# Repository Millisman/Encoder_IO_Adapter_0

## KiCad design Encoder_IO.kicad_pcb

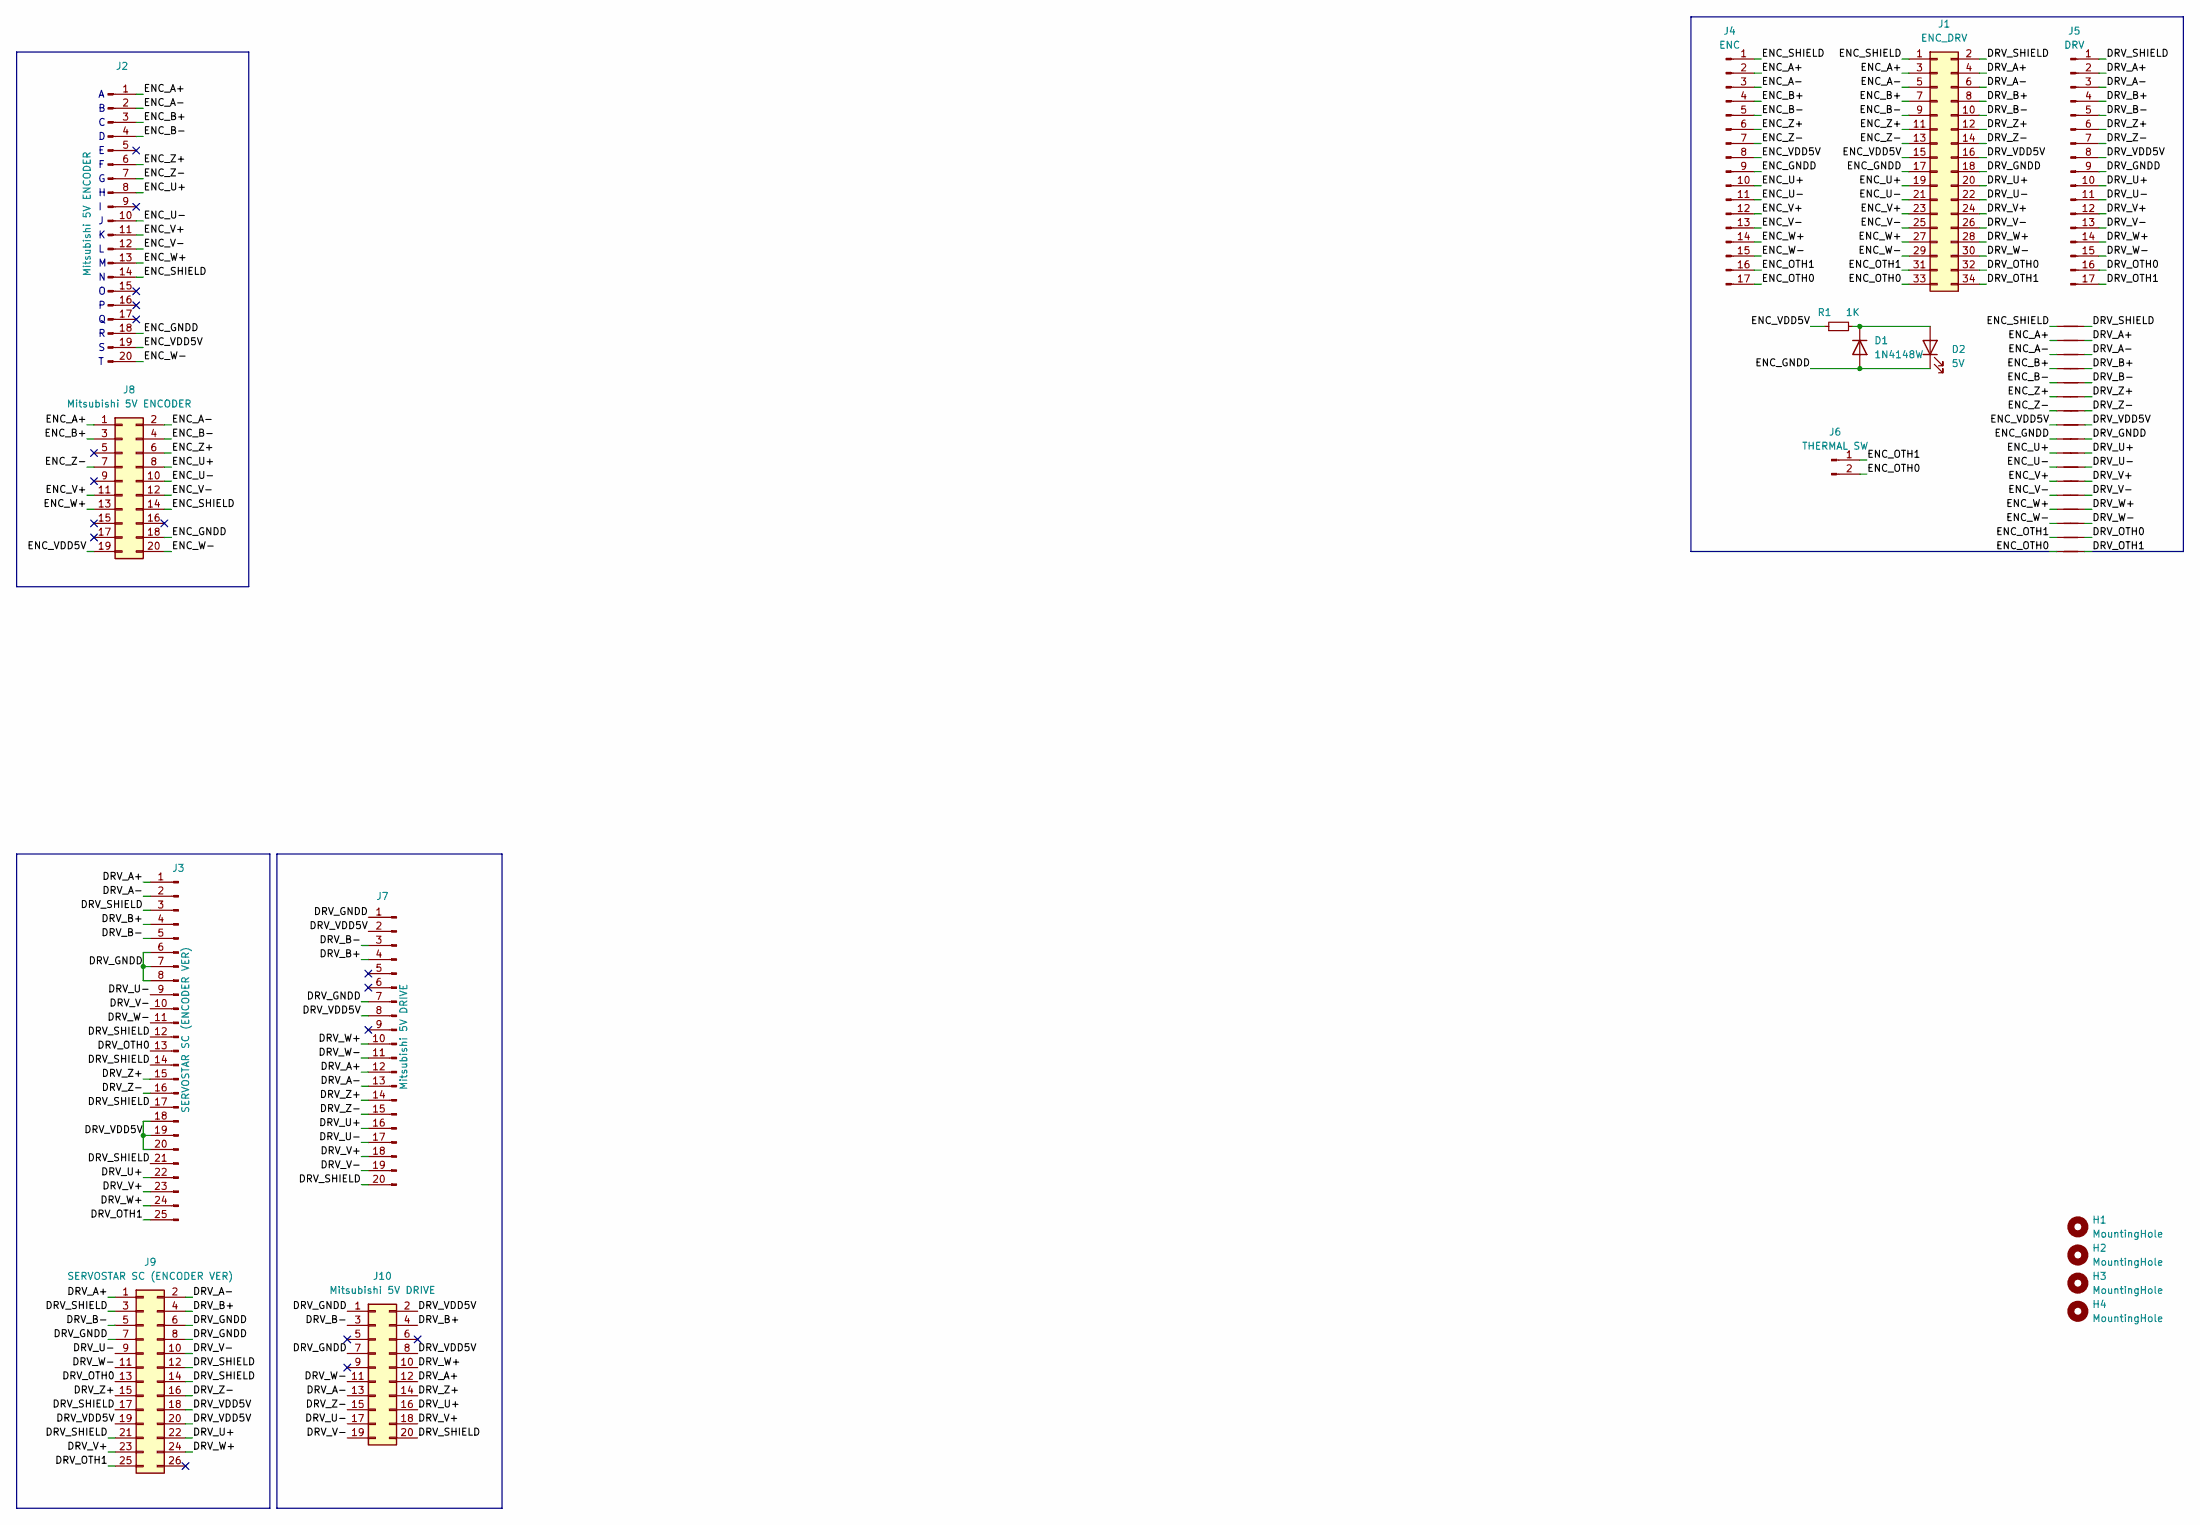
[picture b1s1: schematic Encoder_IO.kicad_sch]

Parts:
D1: 1N4148W; D_SOD-323_HandSoldering
D2: 5V; LED_0805_2012Metric_Pad1.15x1.40mm_HandSolder
H1, H2, H3, H4: MountingHole; MountingHole_3.2mm_M3
J1: ENC_DRV; PinHeader_2x17_P2.54mm_Vertical
J2: Mitsubishi 5V ENCODER; PinHeader_1x20_P2.54mm_Vertical
J3: SERVOSTAR SC (ENCODER VER); PinHeader_1x25_P2.54mm_Vertical
J4: ENC; PinHeader_1x17_P2.54mm_Vertical
J5: DRV; PinHeader_1x17_P2.54mm_Vertical
J6: THERMAL SW; PinHeader_1x02_P2.54mm_Vertical
J7: Mitsubishi 5V DRIVE; PinHeader_1x20_P2.54mm_Vertical
J8: Mitsubishi 5V ENCODER; IDC-Header_2x10_P2.54mm_Vertical
J9: SERVOSTAR SC (ENCODER VER); IDC-Header_2x13_P2.54mm_Vertical
J10: Mitsubishi 5V DRIVE; IDC-Header_2x10_P2.54mm_Vertical
NT1, NT2, NT3, NT4, NT5, NT6, NT7, NT8, NT9, NT10, NT11, NT12, NT13, NT14, NT15, NT16, NT17: NetTie_2; NetTie-2_SMD_Pad0.5mm
R1: 1K; R_0805_2012Metric_Pad1.20x1.40mm_HandSolder

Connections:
/DRV_A+: J1.4, J3.1, J5.2, J7.12, J9.1, J10.12, NT2.2
/DRV_A-: J1.6, J3.2, J5.3, J7.13, J9.2, J10.13, NT3.2
/DRV_B+: J1.8, J3.4, J5.4, J7.4, J9.4, J10.4, NT4.2
/DRV_B-: J1.10, J3.5, J5.5, J7.3, J9.5, J10.3, NT5.2
/DRV_GNDD: J1.18, J3.6, J3.7, J3.8, J5.9, J7.1, J7.7, J9.6, J9.7, J9.8, J10.1, J10.7, NT9.2
/DRV_OTH0: J1.32, J3.13, J5.16, J9.13, NT16.2
/DRV_OTH1: J1.34, J3.25, J5.17, J9.25, NT17.2
/DRV_SHIELD: J1.2, J3.3, J3.12, J3.14, J3.17, J3.21, J5.1, J7.20, J9.3, J9.12, J9.14, J9.17, J9.21, J10.20, NT1.2
/DRV_U+: J1.20, J3.22, J5.10, J7.16, J9.22, J10.16, NT10.2
/DRV_U-: J1.22, J3.9, J5.11, J7.17, J9.9, J10.17, NT11.2
/DRV_V+: J1.24, J3.23, J5.12, J7.18, J9.23, J10.18, NT12.2
/DRV_V-: J1.26, J3.10, J5.13, J7.19, J9.10, J10.19, NT13.2
/DRV_VDD5V: J1.16, J3.18, J3.19, J3.20, J5.8, J7.2, J7.8, J9.18, J9.19, J9.20, J10.2, J10.8, NT8.2
/DRV_W+: J1.28, J3.24, J5.14, J7.10, J9.24, J10.10, NT14.2
/DRV_W-: J1.30, J3.11, J5.15, J7.11, J9.11, J10.11, NT15.2
/DRV_Z+: J1.12, J3.15, J5.6, J7.14, J9.15, J10.14, NT6.2
/DRV_Z-: J1.14, J3.16, J5.7, J7.15, J9.16, J10.15, NT7.2
/ENC_A+: J1.3, J2.1, J4.2, J8.1, NT2.1
/ENC_A-: J1.5, J2.2, J4.3, J8.2, NT3.1
/ENC_B+: J1.7, J2.3, J4.4, J8.3, NT4.1
/ENC_B-: J1.9, J2.4, J4.5, J8.4, NT5.1
/ENC_GNDD: D1.2 (A), D2.1 (K), J1.17, J2.18, J4.9, J8.18, NT9.1
/ENC_OTH0: J1.33, J4.17, J6.2, NT17.1
/ENC_OTH1: J1.31, J4.16, J6.1, NT16.1
/ENC_SHIELD: J1.1, J2.14, J4.1, J8.14, NT1.1
/ENC_U+: J1.19, J2.8, J4.10, J8.8, NT10.1
/ENC_U-: J1.21, J2.10, J4.11, J8.10, NT11.1
/ENC_V+: J1.23, J2.11, J4.12, J8.11, NT12.1
/ENC_V-: J1.25, J2.12, J4.13, J8.12, NT13.1
/ENC_VDD5V: J1.15, J2.19, J4.8, J8.19, NT8.1, R1.1
/ENC_W+: J1.27, J2.13, J4.14, J8.13, NT14.1
/ENC_W-: J1.29, J2.20, J4.15, J8.20, NT15.1
/ENC_Z+: J1.11, J2.6, J4.6, J8.6, NT6.1
/ENC_Z-: J1.13, J2.7, J4.7, J8.7, NT7.1
unnamed: D1.1 (K), D2.2 (A), R1.2

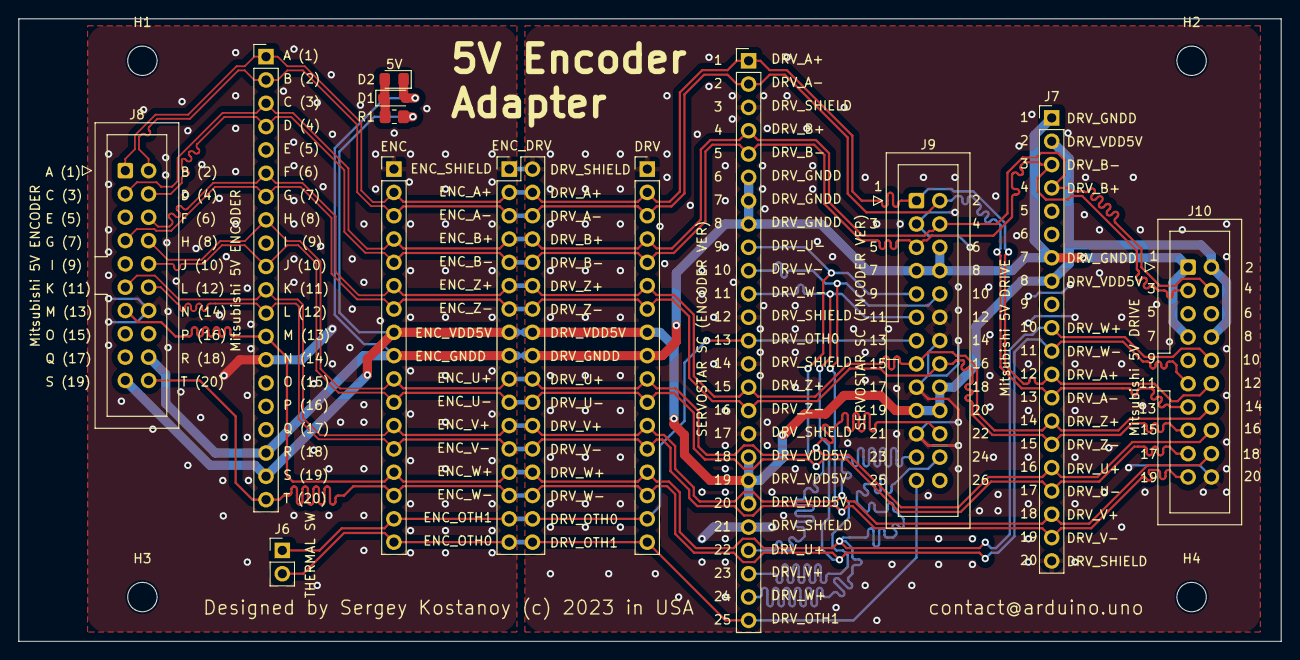
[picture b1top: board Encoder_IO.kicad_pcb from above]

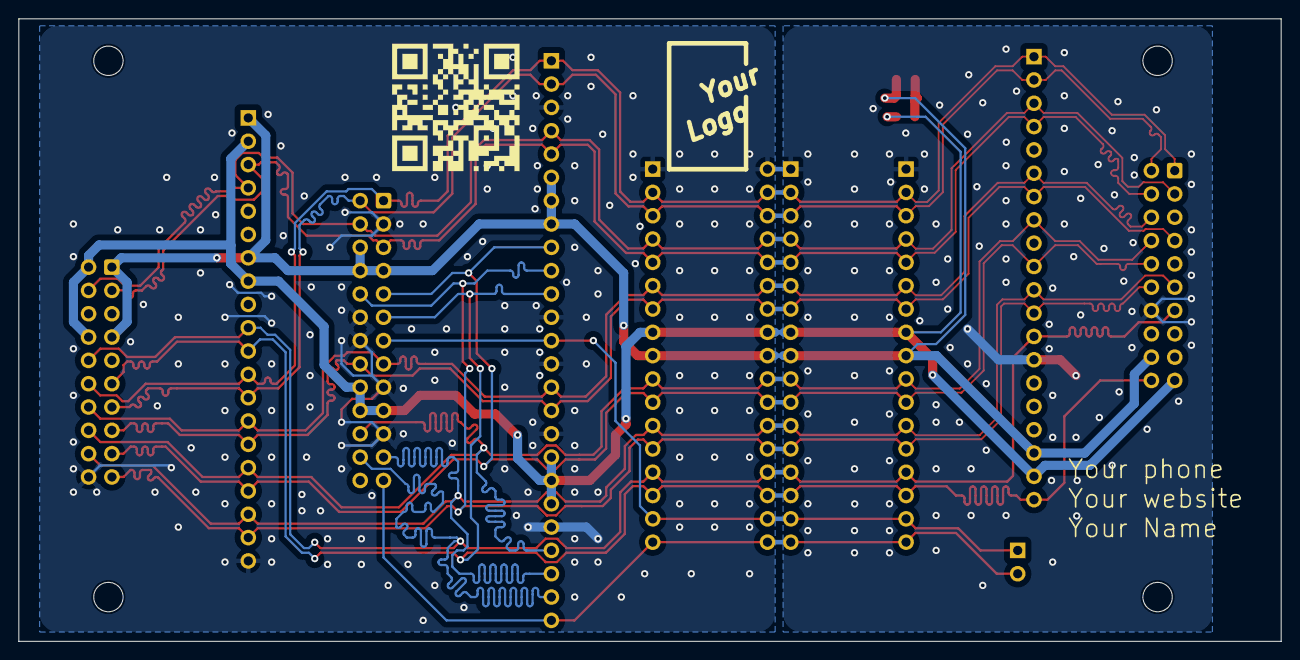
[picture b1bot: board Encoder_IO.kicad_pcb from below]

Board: 2 copper layers, 137.5 x 67.8 mm, 34 parts (17 on the bottom side), 35 nets.

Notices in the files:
Encoder_IO.kicad_pcb:
Designed by Sergey Kostanoy (c) 2023 in USA
